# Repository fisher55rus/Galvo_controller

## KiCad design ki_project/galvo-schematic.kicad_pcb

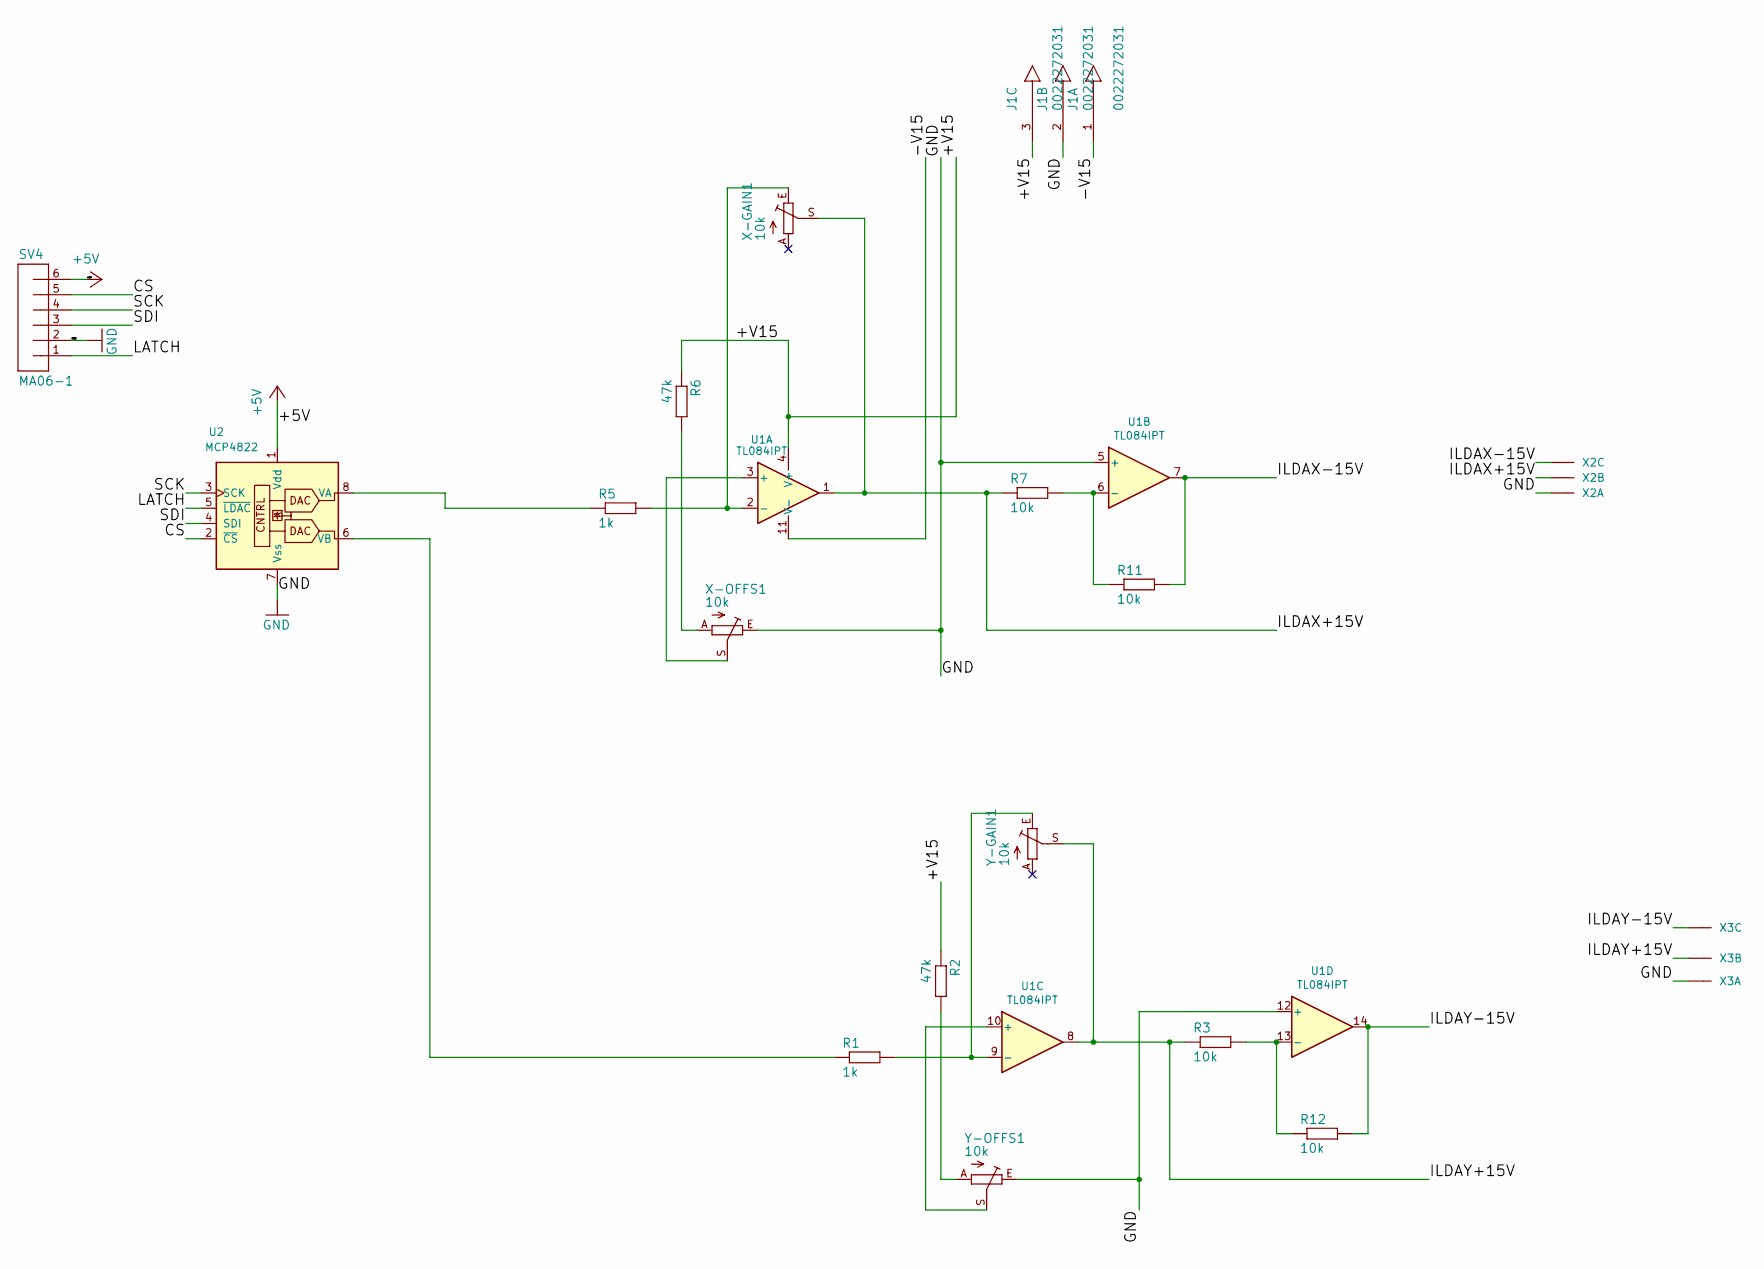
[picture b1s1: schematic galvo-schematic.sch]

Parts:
J1: 0022272031; KK6410-2031_3-PIN
R1, R5: 1k; R_2010_5025Metric_Pad1.52x2.65mm_HandSolder
R2, R6: 47k; R_0603_1608Metric_Pad1.05x0.95mm_HandSolder
R3, R7, R11, R12: 10k; R_0805_2012Metric_Pad1.15x1.40mm_HandSolder
SV4: MA06-1
U1: TL084IPT; TSSOP-14_4.4x5mm_P0.65mm
U2: MCP4822; MSOP-8_3x3mm_P0.65mm
X2, X3: JST-XH-03-PIN-ROUND-PAD; JST-XH-03-PACKAGE-ROUND-PAD
X-GAIN1: 10k; Potentiometer_Murata_PVS3_Vertical
X-OFFS1: 10k; Potentiometer_Murata_PVS3_Vertical
Y-GAIN1: 10k; Potentiometer_Murata_PVS3_Vertical
Y-OFFS1: 10k; Potentiometer_Murata_PVS3_Vertical

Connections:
+5V: SV4.6, U2.1 (Vdd)
/+V15: J1.3, R2.1, R6.1, U1.4 (V+)
/-V15: J1.1, U1.11 (V-)
/CS: SV4.5, U2.2 (~CS)
/ILDAX+15V: R7.1, U1.1, X2.2, X-GAIN1.S
/ILDAX-15V: R11.2, U1.7, X2.3
/ILDAY+15V: R3.1, U1.8, X3.2, Y-GAIN1.S
/ILDAY-15V: R12.2, U1.14, X3.3
/LATCH: SV4.1, U2.5 (~LDAC)
/SCK: SV4.4, U2.3 (SCK)
/SDI: SV4.3, U2.4 (SDI)
GND: J1.2, SV4.2, U1.5 (+), U1.12 (+), U2.7 (Vss), X2.1, X3.1, X-OFFS1.E, Y-OFFS1.E
unnamed: R1.1, U2.6 (VB)
unnamed: R1.2, U1.9 (-), Y-GAIN1.E
unnamed: R2.2, Y-OFFS1.A
unnamed: R5.1, U2.8 (VA)
unnamed: R5.2, U1.2 (-), X-GAIN1.E
unnamed: R6.2, X-OFFS1.A
unnamed: R7.2, R11.1, U1.6 (-)
unnamed: R3.2, R12.1, U1.13 (-)
unnamed: U1.3 (+), X-OFFS1.S
unnamed: U1.10 (+), Y-OFFS1.S

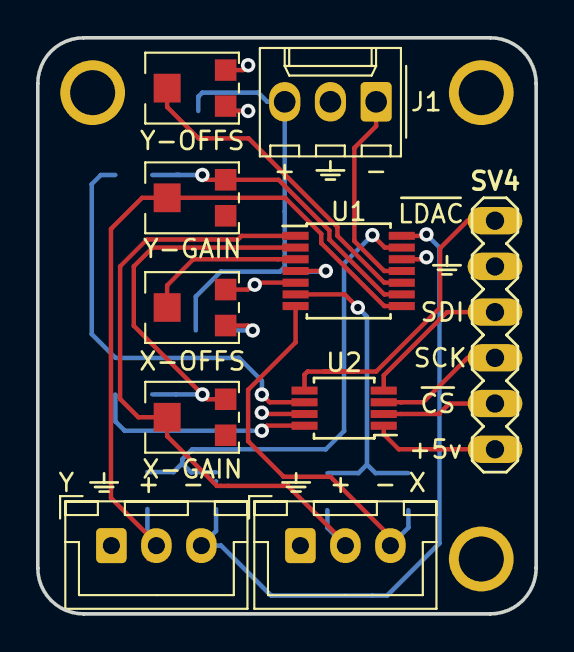
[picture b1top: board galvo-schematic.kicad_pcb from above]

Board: 2 copper layers, 27.7 x 32.0 mm, 18 parts (0 on the bottom side), 22 nets.

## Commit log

2019-04-02 Старый проект, новый прокект, модель, спецификации

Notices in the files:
parts and their libraries:
volks73-Molex: Creative Commons Attribution-ShareAlike 3.0 Unported (CC BY-SA 3.0), http://creativecommons.org/licenses/by-sa/3.0/.
